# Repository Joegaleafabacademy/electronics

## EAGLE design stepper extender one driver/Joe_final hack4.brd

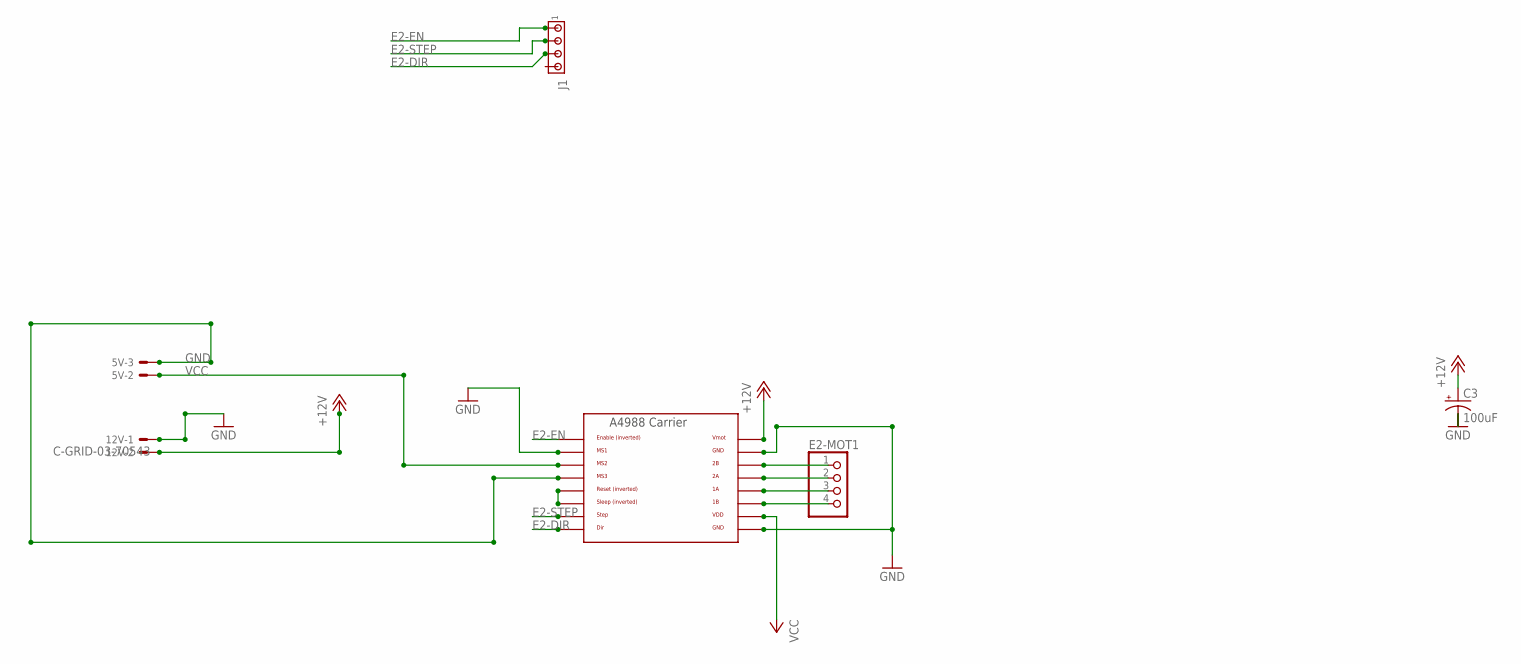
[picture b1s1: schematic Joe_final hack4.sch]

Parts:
5V, 12V: C-GRID-03-70543; 70543-03
C3: 100uF; 153CLV-0605
E2-MOT1: PINHD-1X4; 1X04
J1: MTA04-156; 1X4MTA
U$4: A4988BREAKOUT

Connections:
+12V: 12V.2, C3.+, U$4.VMOT
E2-DIR: J1.3, U$4.DIR
E2-EN: J1.1, U$4.EN
E2-STEP: J1.2, U$4.STEP
GND: 5V.3, 12V.1, C3.-, U$4.GND, U$4.GND@0 (GND), U$4.MS1, U$4.MS3
unnamed: E2-MOT1.1, U$4.2B
unnamed: U$4.RST, U$4.SLP (SLEEP)
unnamed: E2-MOT1.2, U$4.2A
unnamed: E2-MOT1.3, U$4.1A
unnamed: E2-MOT1.4, U$4.1B
VCC: 5V.2, U$4.MS2, U$4.VDD

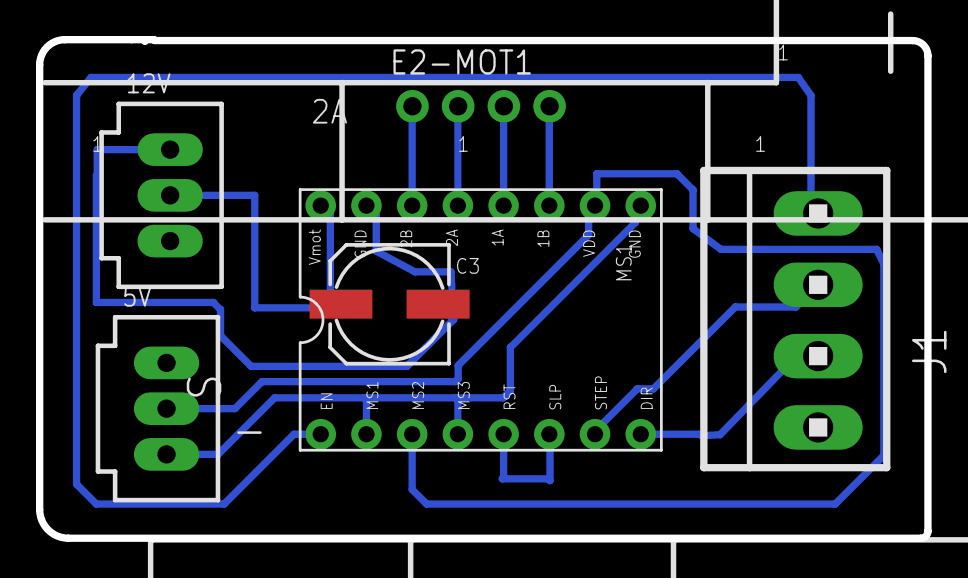
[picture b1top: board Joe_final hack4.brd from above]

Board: 2 copper layers, 49.3 x 27.7 mm, 6 parts (0 on the bottom side), 11 nets.

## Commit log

2016-07-02 final
